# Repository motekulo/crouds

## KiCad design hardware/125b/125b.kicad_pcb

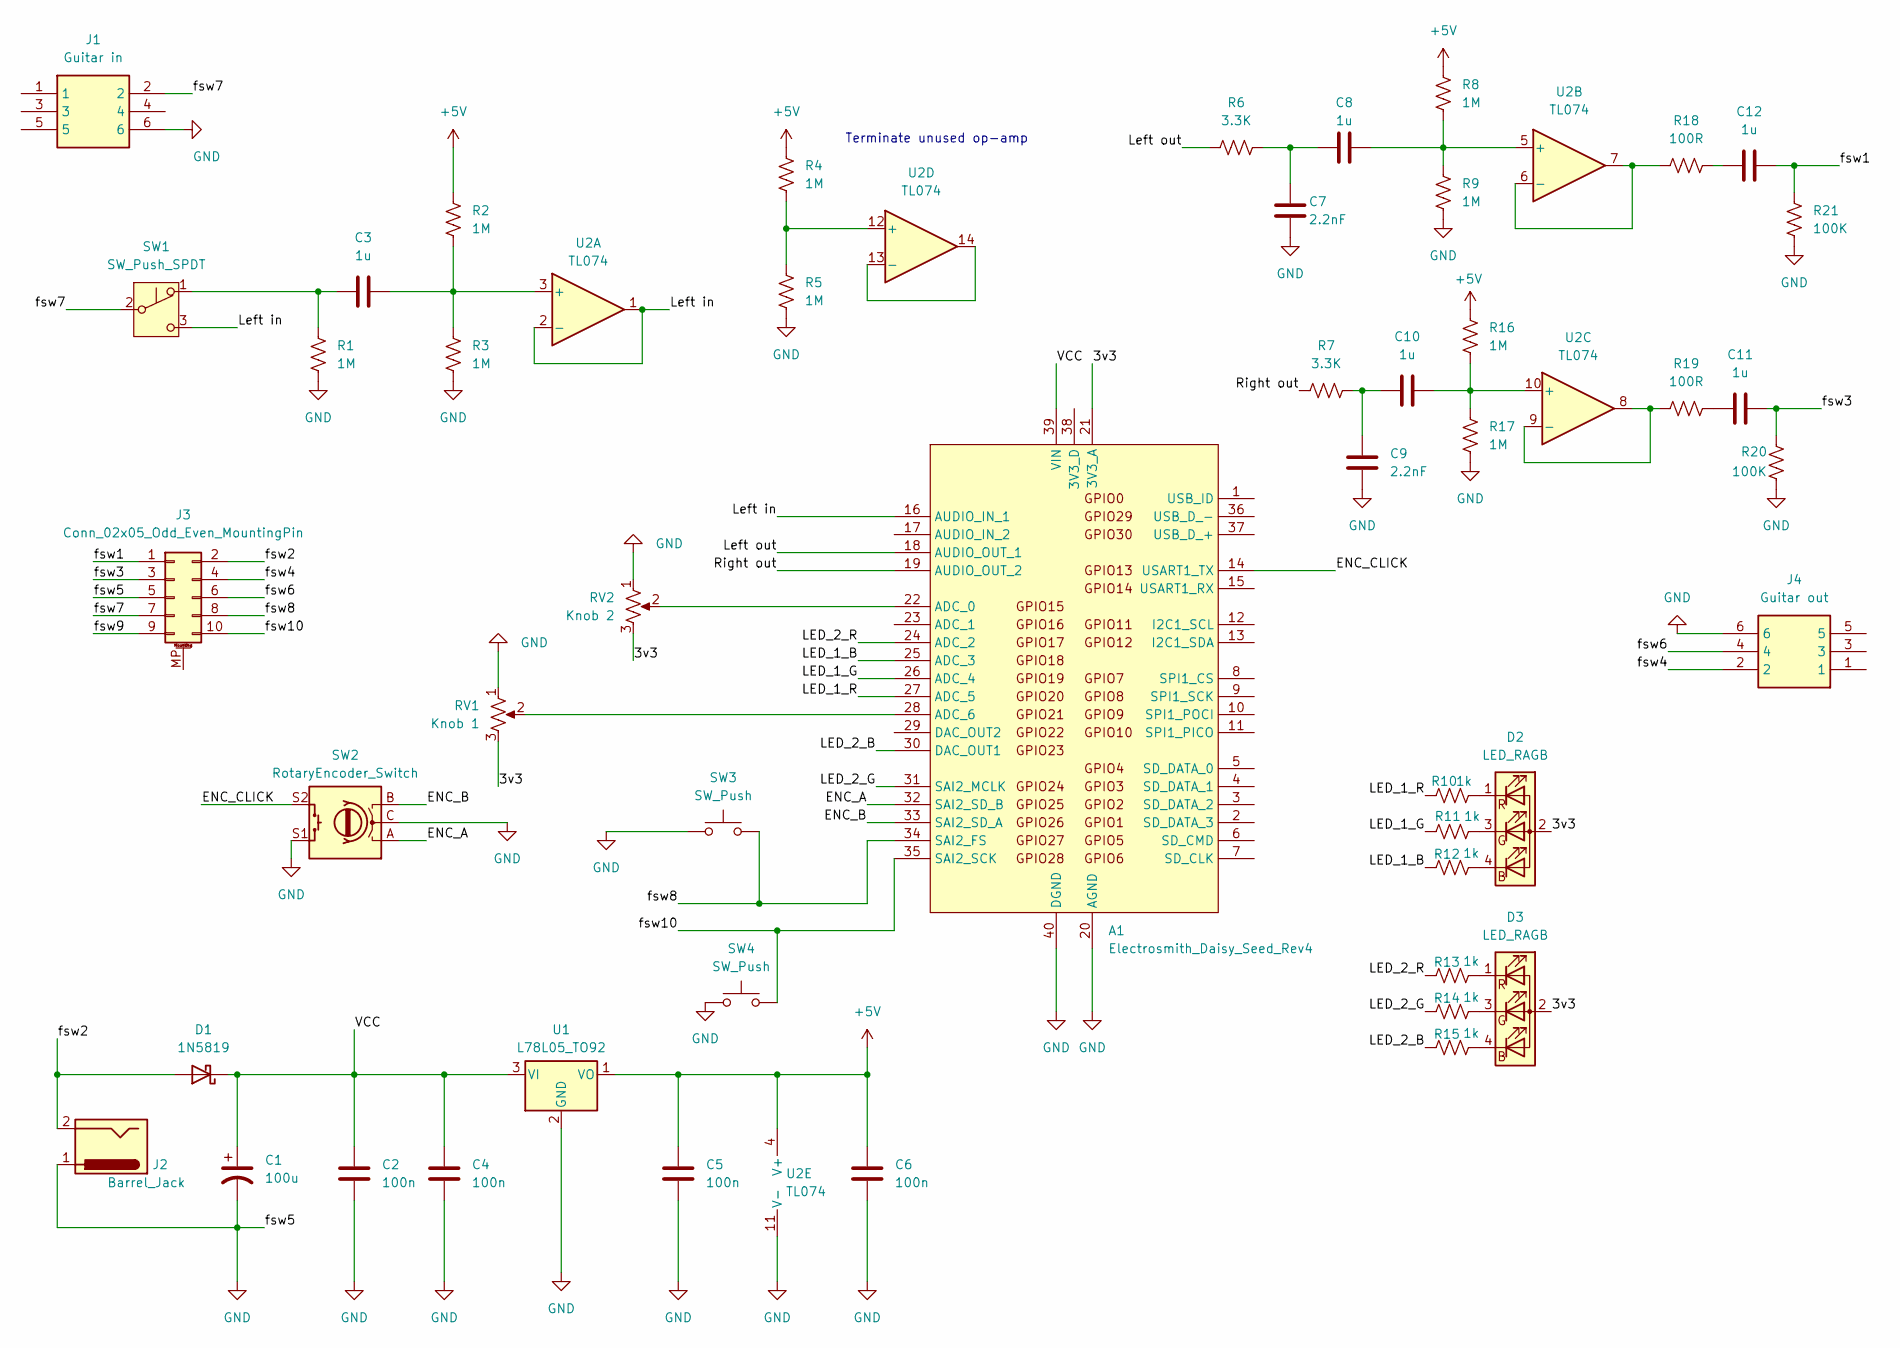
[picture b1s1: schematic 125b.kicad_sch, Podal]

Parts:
A1: Electrosmith_Daisy_Seed_Rev4; Electrosmith_Daisy_Seed
C1: 100u; C_Radial_D5.0mm_H11.0mm_P2.00mm
C2, C4, C5, C6: 100n; C_0805_2012Metric
C3, C8, C10, C11, C12: 1u; C_0805_2012Metric
C7, C9: 2.2nF; C_0805_2012Metric
D1: 1N5819; D_DO-41_SOD81_P7.62mm_Horizontal
D2, D3: LED_RAGB; LED_D5.0mm-4_RGB_Wide_Pins
J1: Guitar in; NYS215; Mouser Part Number 568-NYS215
J2: Barrel_Jack; BarrelJack_Horizontal
J3: Conn_02x05_Odd_Even_MountingPin; IDC-Header_2x05_P2.54mm_Vertical
J4: Guitar out; NYS215; Mouser Part Number 568-NYS215
R1, R2, R3, R4, R5, R8, R9, R16, R17: 1M; R_0805_2012Metric
R6, R7: 3.3K; R_0805_2012Metric
R10, R11, R12, R13, R14, R15: 1k; R_0805_2012Metric
R18, R19: 100R; R_0805_2012Metric
R20, R21: 100K; R_0805_2012Metric
RV1: Knob 1; Potentiometer_Alps_RK09K_Single_Vertical
RV2: Knob 2; Potentiometer_Alps_RK09K_Single_Vertical
SW1: SW_Push_SPDT; Switch_Toggle_SPDT_SubMini
SW2: RotaryEncoder_Switch; RotaryEncoder_Alps_EC12E-Switch_Vertical_H20mm
SW3, SW4: SW_Push; SolderWire-0.5sqmm_1x02_P4.6mm_D0.9mm_OD2.1mm
U1: L78L05_TO92; TO-92_Inline_Wide_78L05_dc
U2: TL074; SOIC-14_3.9x8.7mm_P1.27mm

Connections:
+5V: C5.2, C6.2, R2.1, R4.1, R8.1, R16.1, U1.1 (VO), U2.4 (V+)
/3v3: A1.21 (3V3_A), D2.2 (A), D3.2 (A), RV1.3, RV2.3
/ENC_A: A1.32 (SAI2_SD_B), SW2.A
/ENC_B: A1.33 (SAI2_SD_A), SW2.B
/ENC_CLICK: A1.14 (USART1_TX), SW2.S2
/LED_1_B: A1.25 (ADC_3), R12.1
/LED_1_G: A1.26 (ADC_4), R11.1
/LED_1_R: A1.27 (ADC_5), R10.1
/LED_2_B: A1.30 (DAC_OUT1), R15.1
/LED_2_G: A1.31 (SAI2_MCLK), R14.1
/LED_2_R: A1.24 (ADC_2), R13.1
/Left in: A1.16 (AUDIO_IN_1), SW1.3 (C), U2.1, U2.2 (-)
/Left out: A1.18 (AUDIO_OUT_1), R6.1
/Right out: A1.19 (AUDIO_OUT_2), R7.1
/VCC: A1.39 (VIN), C1.1, C2.2, C4.2, D1.1 (K), U1.3 (VI)
/fsw1: C12.2, J3.1, R21.1
/fsw2: D1.2 (A), J2.2, J3.2
/fsw3: C11.2, J3.3, R20.1
/fsw4: J3.4, J4.2
/fsw6: J3.6, J4.4
/fsw7: J1.2, J3.7, SW1.2 (B)
/fsw8: A1.34 (SAI2_FS), J3.8, SW3.2
/fsw9: J3.9
/fsw10: A1.35 (SAI2_SCK), J3.10, SW4.2
GND: A1.20 (AGND), A1.40 (DGND), C1.2, C2.1, C4.1, C5.1, C6.1, C7.1, C9.1, J1.6, J2.1, J3.5, J4.6, R1.2, R3.2, R5.2, R9.2, R17.2, R20.2, R21.2, RV1.1, RV2.1, SW2.C, SW2.S1, SW3.1, SW4.1, U1.2 (GND), U2.11 (V-)
unnamed: A1.22 (ADC_0), RV2.2
unnamed: A1.28 (ADC_6), RV1.2
unnamed: C7.2, C8.1, R6.2
unnamed: C9.2, C10.1, R7.2
unnamed: C11.1, R19.2
unnamed: C12.1, R18.2
unnamed: D2.4 (BK), R12.2
unnamed: D2.3 (GK), R11.2
unnamed: D2.1 (RK), R10.2
unnamed: D3.4 (BK), R15.2
unnamed: D3.3 (GK), R14.2
unnamed: D3.1 (RK), R13.2
unnamed: C3.1, R1.1, SW1.1 (A)
unnamed: C3.2, R2.2, R3.1, U2.3 (+)
unnamed: C8.2, R8.2, R9.1, U2.5 (+)
unnamed: R18.1, U2.6 (-), U2.7
unnamed: C10.2, R16.2, R17.1, U2.10 (+)
unnamed: R19.1, U2.8, U2.9 (-)
unnamed: R4.2, R5.1, U2.12 (+)
unnamed: U2.13 (-), U2.14

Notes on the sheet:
Terminate unused op-amp

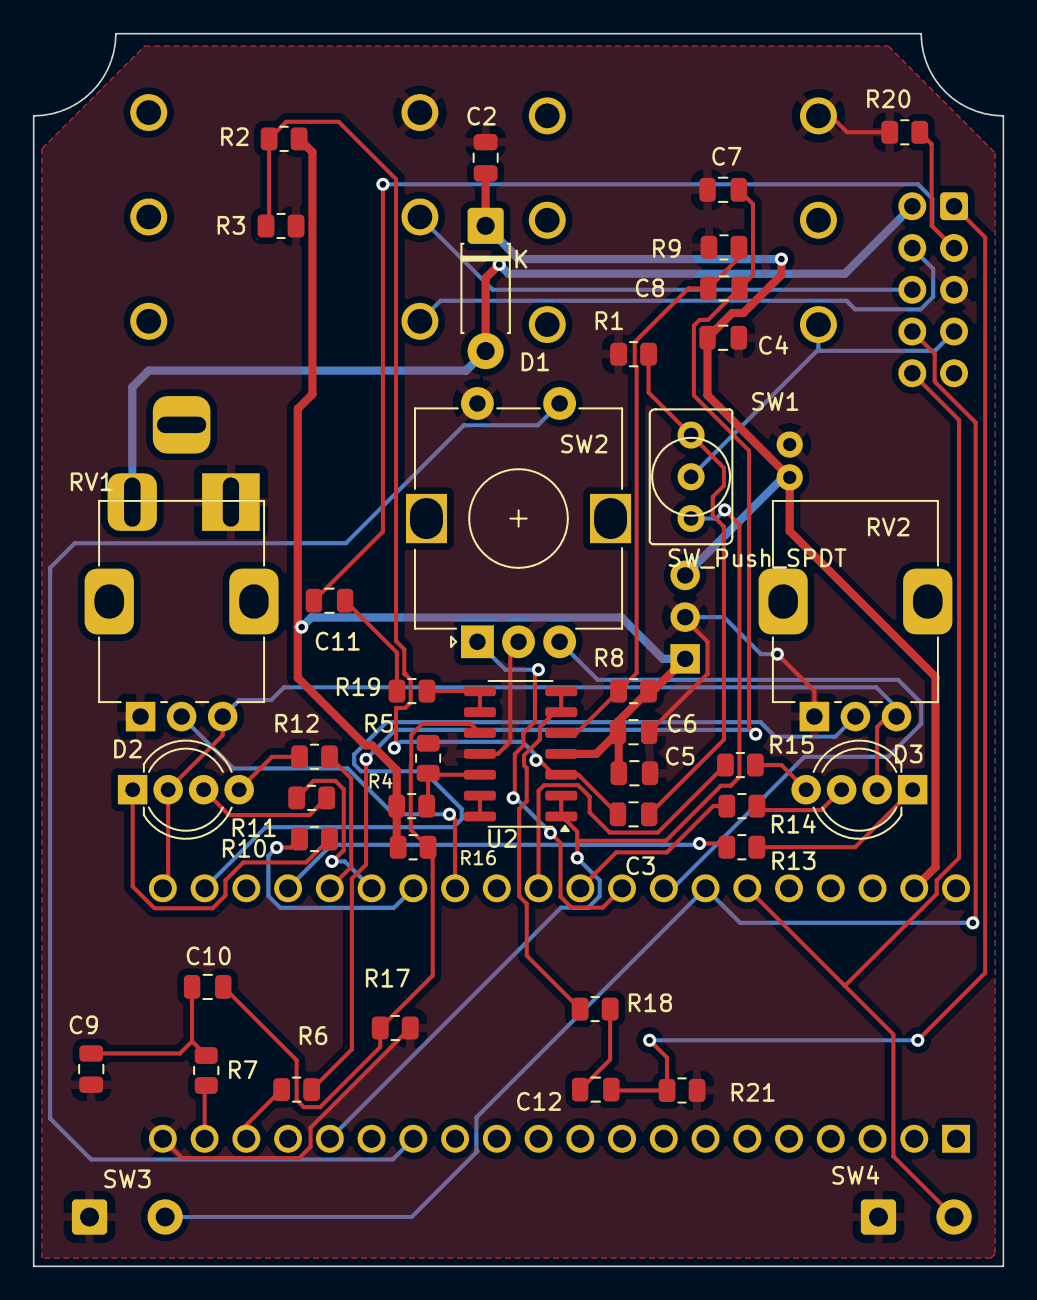
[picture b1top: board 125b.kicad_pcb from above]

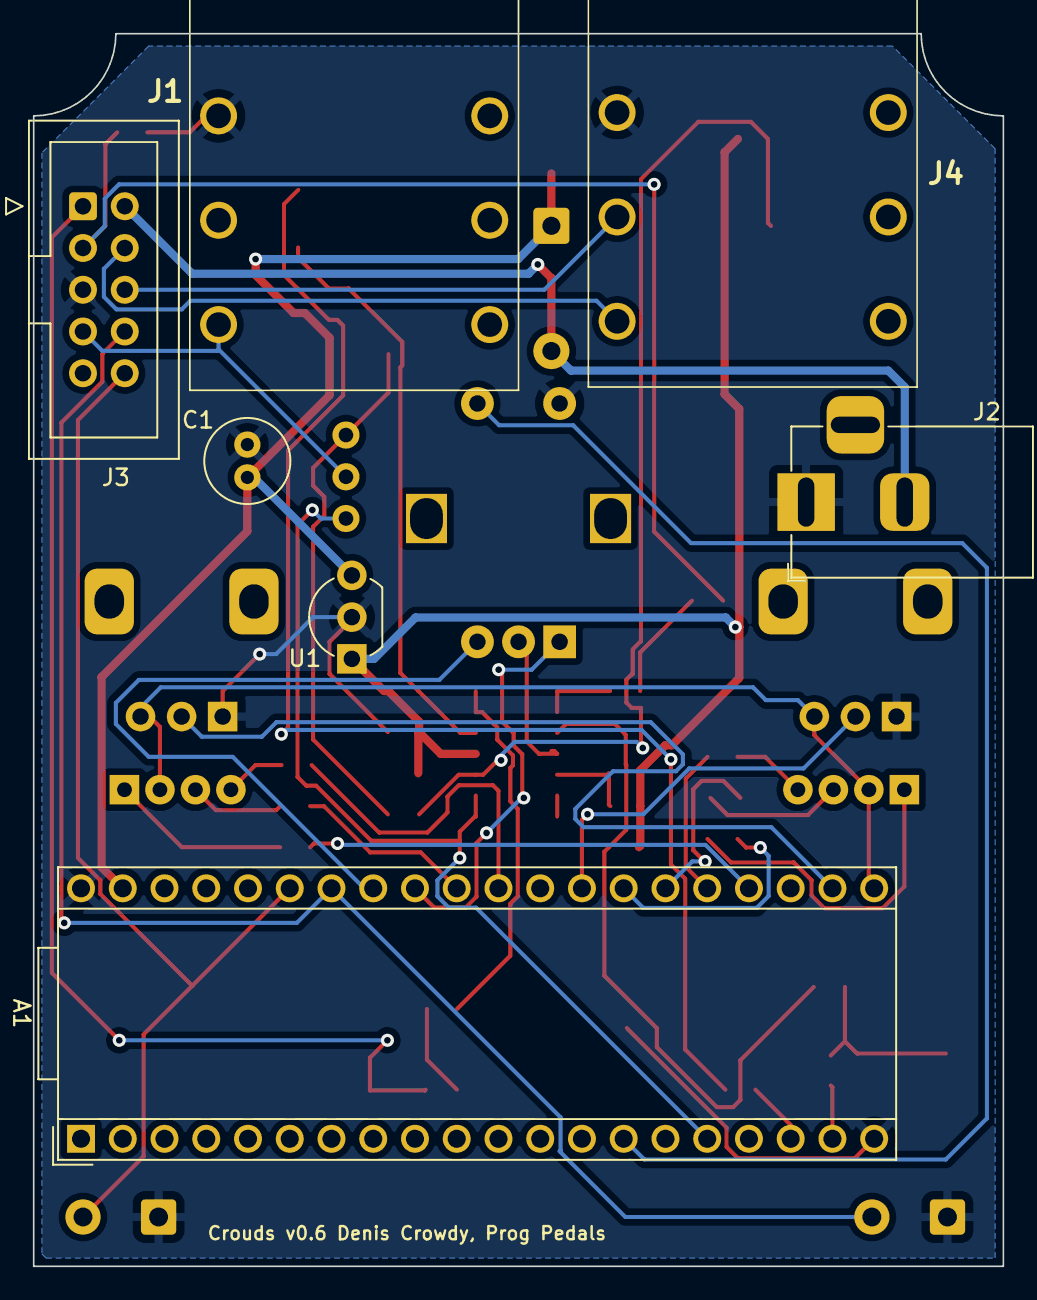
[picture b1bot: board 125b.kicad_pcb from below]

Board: 2 copper layers, 59.0 x 75.0 mm, 49 parts (7 on the bottom side), 44 nets.

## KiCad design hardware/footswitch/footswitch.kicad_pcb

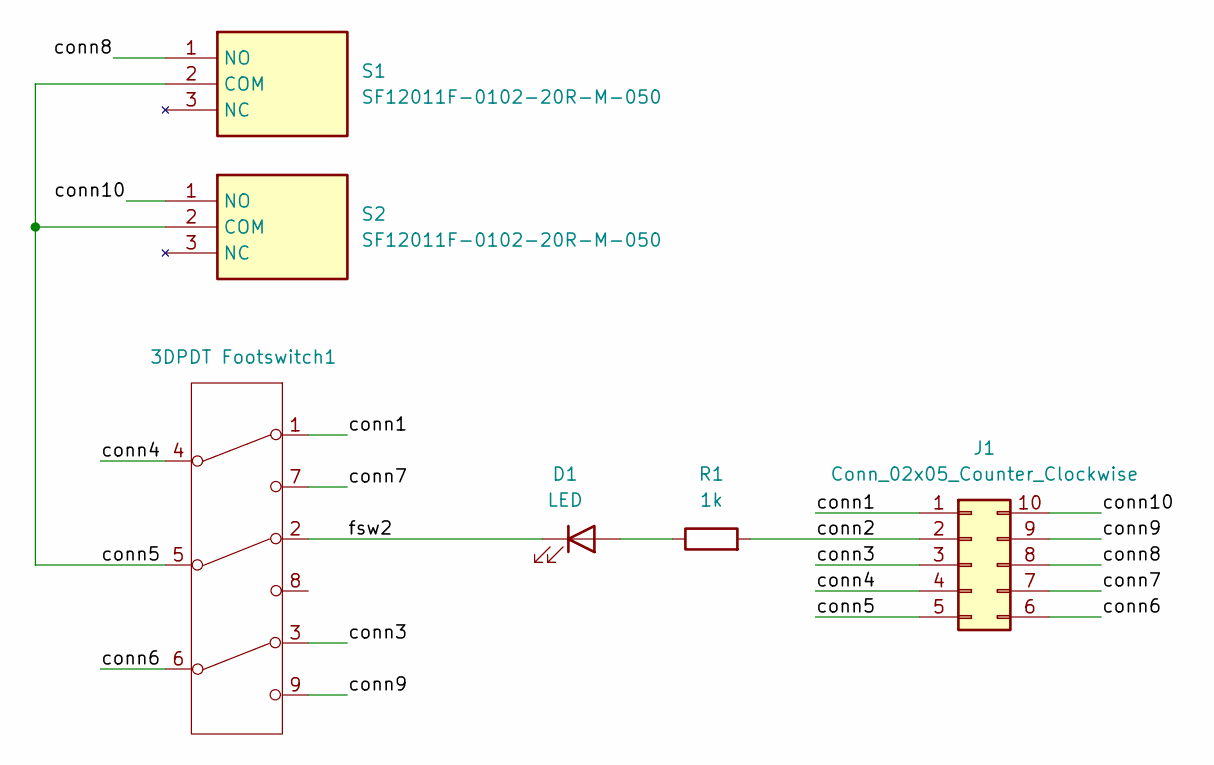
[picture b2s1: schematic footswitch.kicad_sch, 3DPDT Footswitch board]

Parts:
3DPDT Footswitch1: Switches_Stomp_Switch_3PDT
D1: LED; LED_D1.8mm_W3.3mm_H2.4mm
J1: Conn_02x05_Counter_Clockwise; IDC-Header_2x05_P2.54mm_Vertical
R1: 1k; R_Axial_DIN0207_L6.3mm_D2.5mm_P10.16mm_Horizontal
S1, S2: SF12011F-0102-20R-M-050; SF12011F010220RM050; Mouser Part Number 107-SF12011F-102-M

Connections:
/conn1: 3DPDT Footswitch1.1 (A), J1.1
/conn2: J1.2, R1.2
/conn3: 3DPDT Footswitch1.3 (C), J1.3
/conn4: 3DPDT Footswitch1.4 (D), J1.4
/conn5: 3DPDT Footswitch1.5 (E), J1.5, S1.2 (COM), S2.2 (COM)
/conn6: 3DPDT Footswitch1.6 (F), J1.6
/conn7: 3DPDT Footswitch1.7 (G), J1.7
/conn8: J1.8, S1.1 (NO)
/conn9: 3DPDT Footswitch1.9 (G), J1.9
/conn10: J1.10, S2.1 (NO)
/fsw2: 3DPDT Footswitch1.2 (B), D1.1 (K)
unnamed: D1.2 (A), R1.1

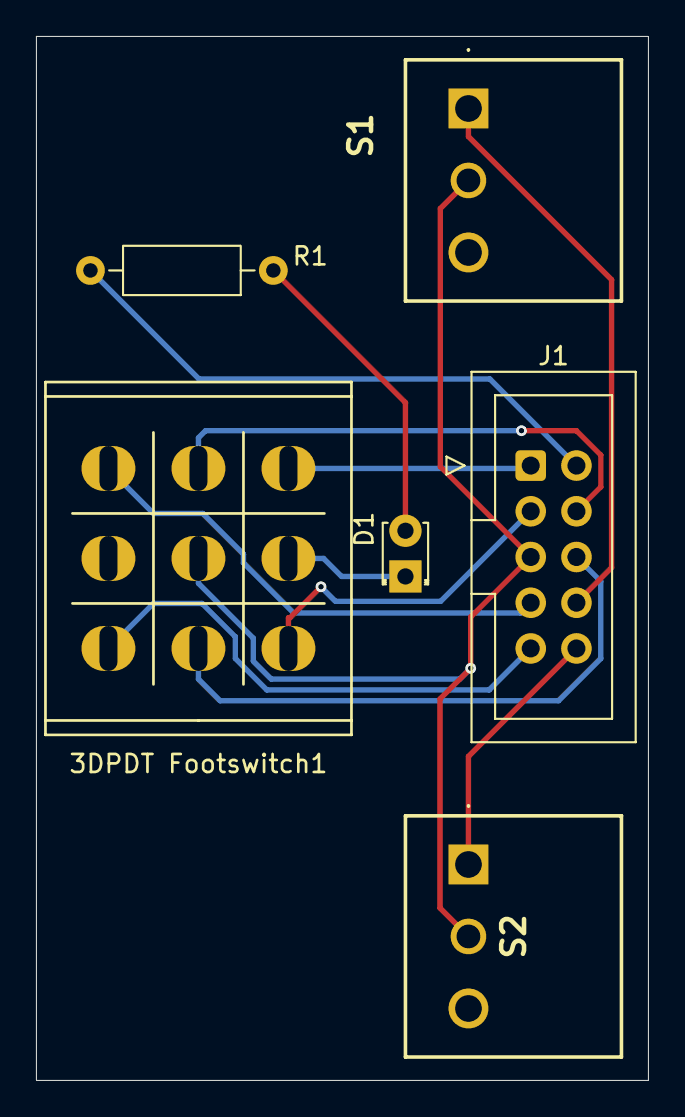
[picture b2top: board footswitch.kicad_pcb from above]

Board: 2 copper layers, 34.0 x 58.0 mm, 6 parts (0 on the bottom side), 12 nets.

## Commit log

2025-09-11 Add and adjust drill template files for v0.5
2025-09-15 Adapt board for pcb mounted footswitches
2025-09-17 Send switches to IDC; spdt for line level
    Also fix line level to go straight to left in
2025-09-17 get new stereo sockets on schematic and pcb
2025-09-17 Wire connectors for push switches and add slide spdt
2025-09-17 Retraced and various parts moved and adjusted
